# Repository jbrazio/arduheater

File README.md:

# Arduheater
Arduheater is a full open source intelligent heat strip controller for astronomy usage.

# Motivation
Controlling dew is a big thing if you really intent to do astronomy all year around.
This project will allow you to build a four channel intelligent heat strip contoller for less than 10€.

# Design Goals

## 1. Remotely controllable
This was a very important part of the design, most heat controllers, specially the DIY ones, rely on the PWM signal for each channel being manually adjusted by means of a potentiometer. This either requires the user to be near the device tweeking it or to set it to a temperature that may be higher than the one really needed thus completely trashing efficiency. Arduheater uses a serial connection so you can use any USB-Serial-TTL dongle to adjust it's settings either you're 2 or 2000 meters away.

## 2. Efficient energy usage
Manual adjusted heater will either require the user to be tweeking it or they will wast more energy than necessary due to the general tendency to use a higher that required setpoint, this is valid for any PWM or bang-bang style controllers. Arduheater uses a temperature sensor (DHT22) to measure basic environmental properties such as temperature and humidity, knowing them both makes the calculation of the dew point[1] possible. Arduheater also has a temperature sensor (NTC) for each heating strip, allowing the micro-controller to have a rough estimation of the temperature the equipment is at; it will be a rough estimation because we are really interested on the lenses surface temperature but we are actually measuring the heat strip temperature, to mitigate this, Arduheater allows the user to set specific offsets per heating strip.

Arduheater uses a PID controller[2] to efficiently manage the energy so only the required amount of energy to maintain a temperature setpoint is delivered to the heating strip. This is possible due the usage of a PWM signal while driving the outputs; the delta between the environmental dew point (plus offset, i.e. setpoint) and the heating strip temperature will make the micro-controller output a PID-calculated PWM signal until this delta reaches zero. In practical terms if a 12V heating strip full on consumes 12W of power (1A) it may be possible for it to use only 1W or even less to keep the equipment above dewpoint and the power usage will be automatically updated during the night as conditions vary, so the system will be always using the least amount of power to keep the dew away.

[1] Dew point is that dreadful threshold at which water condensation starts to happen on the lenses/equipment.

[2] A proportional–integral–derivative controller (PID controller) is a control loop feedback mechanism (controller) commonly used in industrial control systems.

## 3. Builder friendly
Using off-the-shelf components such as the Arduino Nano and easily available parts Arduheater is aimed to be build by anyone with a soldering iron and some patience, no degree in electronics required.

## 4. Multiple independent channels
Each of the four outputs have independent controls such as offset, min and max output power and of course the three main properties of the PID controller (Kp, Ki and Kd).

# Hardware
It was built on top of a standard ATmega 328 Arduino such as UNO, Pro or Nano; currently it does not support the Mega or any other ARM based board.

## BOM

Qty  | Value     | Device              | Size   | Package
---: | :-------- | :------------------ | :----- | :------
1    | Nano 328P | Arduino             |        |
1    | 10uF      | Capacitor Polarized | "Ø5x11 | THT
1    | AM2320    | Probe               |        | THT
4    | 100nF     | Capacitor Ceramic   | 3216   | SMD
4    | 1K        | Resistor            | 3216   | SMD
4    | 1N4004    | Diode               |        | DO41
4    | IRF3205   | N-MOSFET            |        | TO220
4    | EL817     | Optocoupler         |        | DIP4
4    | Red       | LED 3mm             |        | THT
4    | 10K       | NTC                 |        | THT
4    | M+F kit   | XLR                 | 12mm   | GX12
5    | 2P        | Screw Terminal      | 5mm    | THT
8    | 220R      | Resistor            | 3216   | SMD
9    | 10K       | Resistor            | 3216   | SMD

Note: It is *very* important to have a inline fuse on the 12V feed line.

## 3D printed parts
To download and print instructions for the 3D printed parts have a look at the [Thing #2614341][2614341].

[2614341]: https://www.thingiverse.com/thing:2614341

## PCB and Schematic
For the complete Eagle files have a look at the [PCB](./doc/pcb/) folder, as an alternative you may perfer to build the [Preforated Board](./doc/prefboard/) version.

# License
[GNU GPLv3](./LICENSE).

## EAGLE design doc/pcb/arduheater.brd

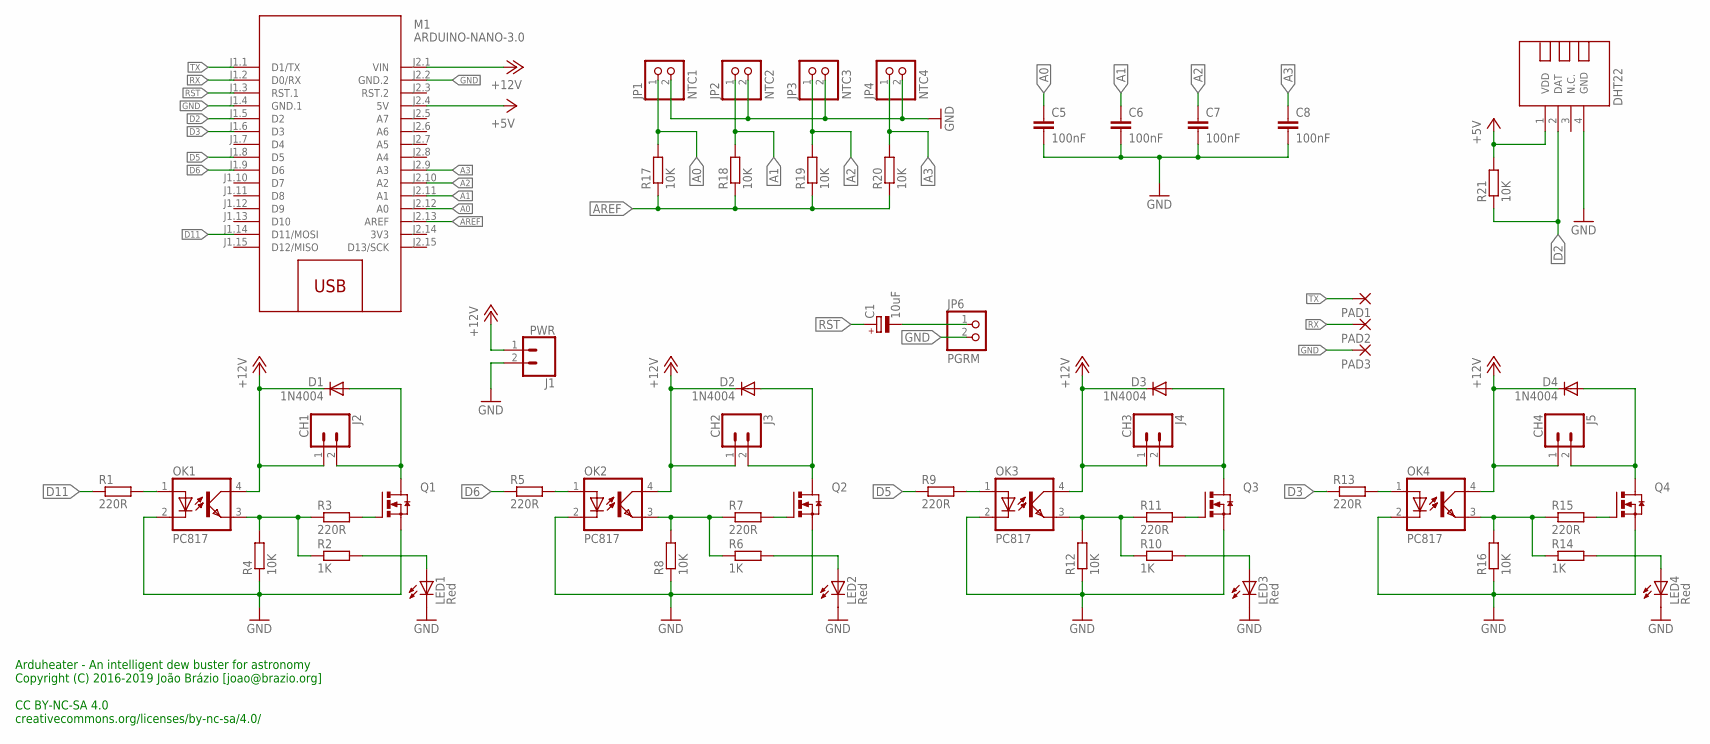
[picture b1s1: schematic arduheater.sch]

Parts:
C1: 10uF; E2,5-6E
C5, C6, C7, C8: 100nF; C3216
D1, D2, D3, D4: 1N4004; DO41-10
DHT22: TEMP-HUM-SENSOR-DHT22
J1: PWR; SCREWTERMINAL-5MM-2
J2: CH1; SCREWTERMINAL-5MM-2
J3: CH2; SCREWTERMINAL-5MM-2
J4: CH3; SCREWTERMINAL-5MM-2
J5: CH4; SCREWTERMINAL-5MM-2
JP1: NTC1; 1X02
JP2: NTC2; 1X02
JP3: NTC3; 1X02
JP4: NTC4; 1X02
JP6: PGRM; 1X02
LED1, LED2, LED3, LED4: Red; LED5MM
M1: ARDUINO-NANO-3.0
OK1, OK2, OK3, OK4: PC817; DIL04
PAD1, PAD2, PAD3: SMD2; SMD1,27-2,54
Q1, Q2, Q3, Q4: IRF3704L-V; TO262-V
R1, R3, R5, R7, R9, R11, R13, R15: 220R; M1206
R2, R6, R10, R14: 1K; M1206
R4, R8, R12, R16, R17, R18, R19, R20, R21: 10K; M1206

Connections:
3V3: M1.J2.14 (3V3)
+5V: DHT22.1 (VDD), M1.J2.4 (5V), R21.2
+12V: D1.C, D2.C, D3.C, D4.C, J1.1, J2.1, J3.1, J4.1, J5.1, M1.J2.1 (VIN), OK1.4 (COL), OK2.4 (COL), OK3.4 (COL), OK4.4 (COL)
A0: C5.1, JP1.1, M1.J2.12 (A0), R17.2
A1: C6.1, JP2.1, M1.J2.11 (A1), R18.2
A2: C7.1, JP3.1, M1.J2.10 (A2), R19.2
A3: C8.1, JP4.1, M1.J2.9 (A3), R20.2
AREF: M1.J2.13 (AREF), R17.1, R18.1, R19.1, R20.1
D2: DHT22.2 (DAT), M1.J1.5 (D2), R21.1
D3: M1.J1.6 (D3), R13.1
D5: M1.J1.8 (D5), R9.1
D6: M1.J1.9 (D6), R5.1
D11: M1.J1.14 (D11/MOSI), R1.1
GND: C5.2, C6.2, C7.2, C8.2, DHT22.4 (GND), J1.2, JP1.2, JP2.2, JP3.2, JP4.2, JP6.2, LED1.K (C), LED2.K (C), LED3.K (C), LED4.K (C), M1.J1.4 (GND.1), M1.J2.2 (GND.2), OK1.2 (C), OK2.2 (C), OK3.2 (C), OK4.2 (C), PAD3.1, Q1.3 (S), Q2.3 (S), Q3.3 (S), Q4.3 (S), R4.1, R8.1, R12.1, R16.1
unnamed: OK1.1 (A), R1.2
unnamed: Q1.1 (G), R3.2
unnamed: OK2.1 (A), R5.2
unnamed: OK1.3 (EMIT), R2.1, R3.1, R4.2
unnamed: LED2.A, R6.2
unnamed: D1.A, J2.2, Q1.2 (D)
unnamed: OK2.3 (EMIT), R6.1, R7.1, R8.2
unnamed: Q2.1 (G), R7.2
unnamed: C1.-, JP6.1
unnamed: D2.A, J3.2, Q2.2 (D)
unnamed: OK3.1 (A), R9.2
unnamed: LED3.A, R10.2
unnamed: OK3.3 (EMIT), R10.1, R11.1, R12.2
unnamed: Q3.1 (G), R11.2
unnamed: D3.A, J4.2, Q3.2 (D)
unnamed: OK4.1 (A), R13.2
unnamed: LED4.A, R14.2
unnamed: OK4.3 (EMIT), R14.1, R15.1, R16.2
unnamed: Q4.1 (G), R15.2
unnamed: D4.A, J5.2, Q4.2 (D)
unnamed: LED1.A, R2.2
RST: C1.+, M1.J1.3 (RST.1)
RX: M1.J1.2 (D0/RX), PAD2.1
TX: M1.J1.1 (D1/TX), PAD1.1

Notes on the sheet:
DHT22
Arduheater - An intelligent dew buster for astronomy Copyright (C) 2016-2019 João Brázio [joao@brazio.org] CC BY-NC-SA 4.0 creativecommons.org/licenses/by-nc-sa/4.0/

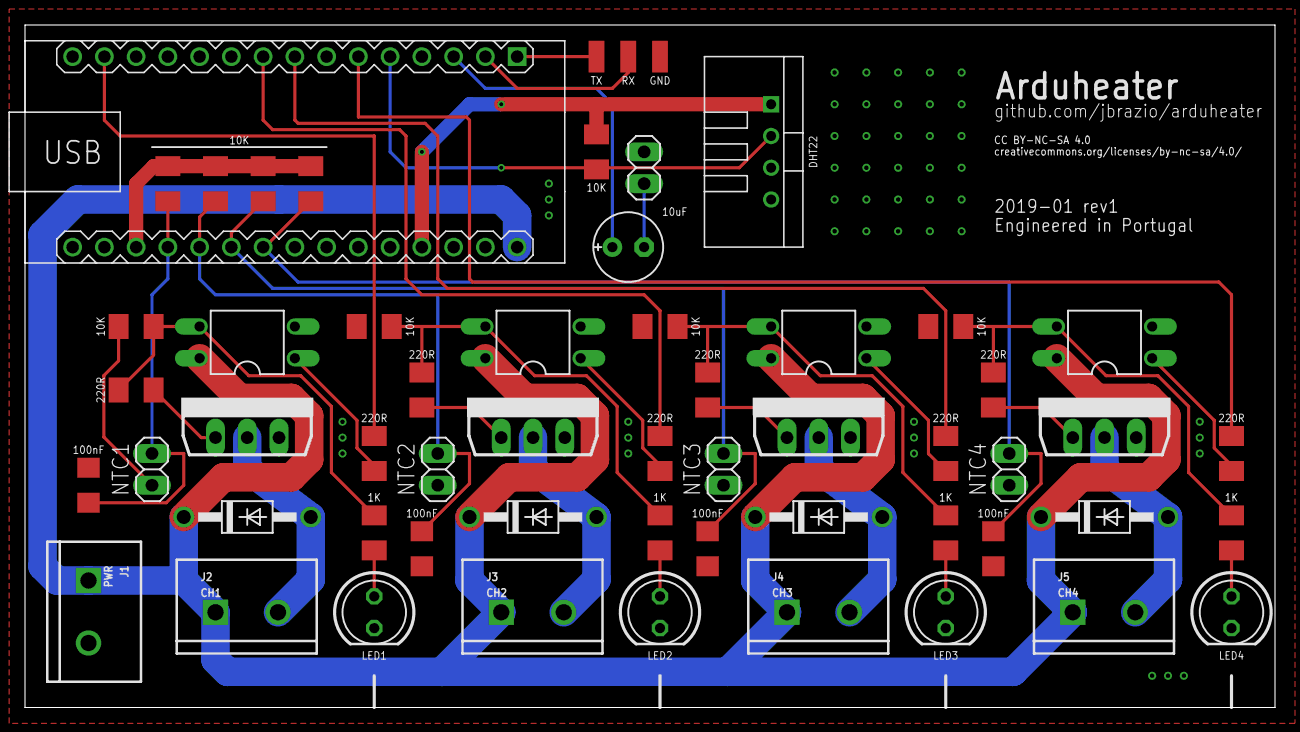
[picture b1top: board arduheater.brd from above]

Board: 2 copper layers, 100.0 x 54.6 mm, 57 parts (0 on the bottom side), 37 nets.

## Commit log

2017-02-14 Initial import of the source code
2017-02-14 Implemented platformio folder structure
2017-02-14 Started using namespaces Implemented serial print functions Removed most forced code optimizations
2017-02-14 Marked u8glibc as a git submodule
2017-02-14 Stopped inlining all serial print functions
2017-02-14 Added include dependencies to each src file
2017-02-14 Implemented the card and painter concept General code cleanup and optimizations General platformio tree cleanup Removed u8glib as a git submodule and added it to pio depedency list Updated copyright 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
2017-02-14 Implemented DHT22 and moving mean smoothing algorithm Code tree cleanup
2017-02-14 Implemented the (still non func) serial object
2017-02-15 Serial is now fully functional on the 328p
2017-02-15 Started the implementation of widgets Created dummy files for the ADC functionality
2017-02-25 Major changeset, implemented PID
2017-02-25 Updated git and platformio settings
2017-03-10 Another major changeset
2017-03-13 Menu movement kinda working
2017-03-14 Rework the card class
2017-03-16 Heater channel offset prototype
2017-03-17 Major rework branch init
2017-03-17 NTC and DHT22 fully working
2017-03-20 Implemented a (still) non-working PID autotune
2017-03-21 Implemented serial commandline
2017-03-21 PID autotune is working
2017-03-21 Start of eeprom implementation
2017-03-22 Implemented eeprom load, save and defaults
2017-03-26 EEPROM save and load done
2017-03-28 All offset working, improved PID algorithm
2017-04-10 Miscellaneous trivial changes
2017-04-11 Fixed the static bug inside PID
2017-04-13 ISR will now control the heater based on a register flag
2017-04-21 Relaxed the thermistor error detection process
2017-04-21 PID autotune debug
2017-05-29 Updated the README file
2017-05-30 Fixed a typo
2017-05-30 Improved config file comments
2017-05-30 Code cleanup
2017-05-30 Travis configuration
2017-09-15 Improved PID performance
2017-10-30 Added project's schematic and updated the README file
2017-11-03 Updated the schematic so the TIP120 is now being driven at full saturation mode
2017-11-16 Code refactoring
2018-03-11 Most chuncks of the code are now ready, still missing glue logic between it all
2018-05-04 Mostly working version
2018-05-04 Update release version
2018-09-03 Waveform generation improvement and misc changes to the source tree
2018-10-07 Update HAL
2019-01-25 Added Eagle PCB and Schematic
2019-01-31 Update copyright notice
2019-02-01 Float harmonization
2019-02-01 Implements ambient temp and rh offset config
2019-03-07 Implements eeprom settings
2019-04-16 Enable Probot Stale and update the README file
2019-04-18 Update main logo
2019-04-18 Update Travis CI badge
2019-06-17 Update README.md
    BOM list updated

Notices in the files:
parts and their libraries:
diy-modules: Released under the Creative Commons Attribution 4.0 International License: http://creativecommons.org/licenses/by/4.0
SparkFun-Connectors: Licensing: Creative Commons ShareAlike 4.0 International - https://creativecommons.org/licenses/by-sa/4.0
